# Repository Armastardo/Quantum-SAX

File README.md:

# Quantum-SAX
Digital controller powered by a RP2040

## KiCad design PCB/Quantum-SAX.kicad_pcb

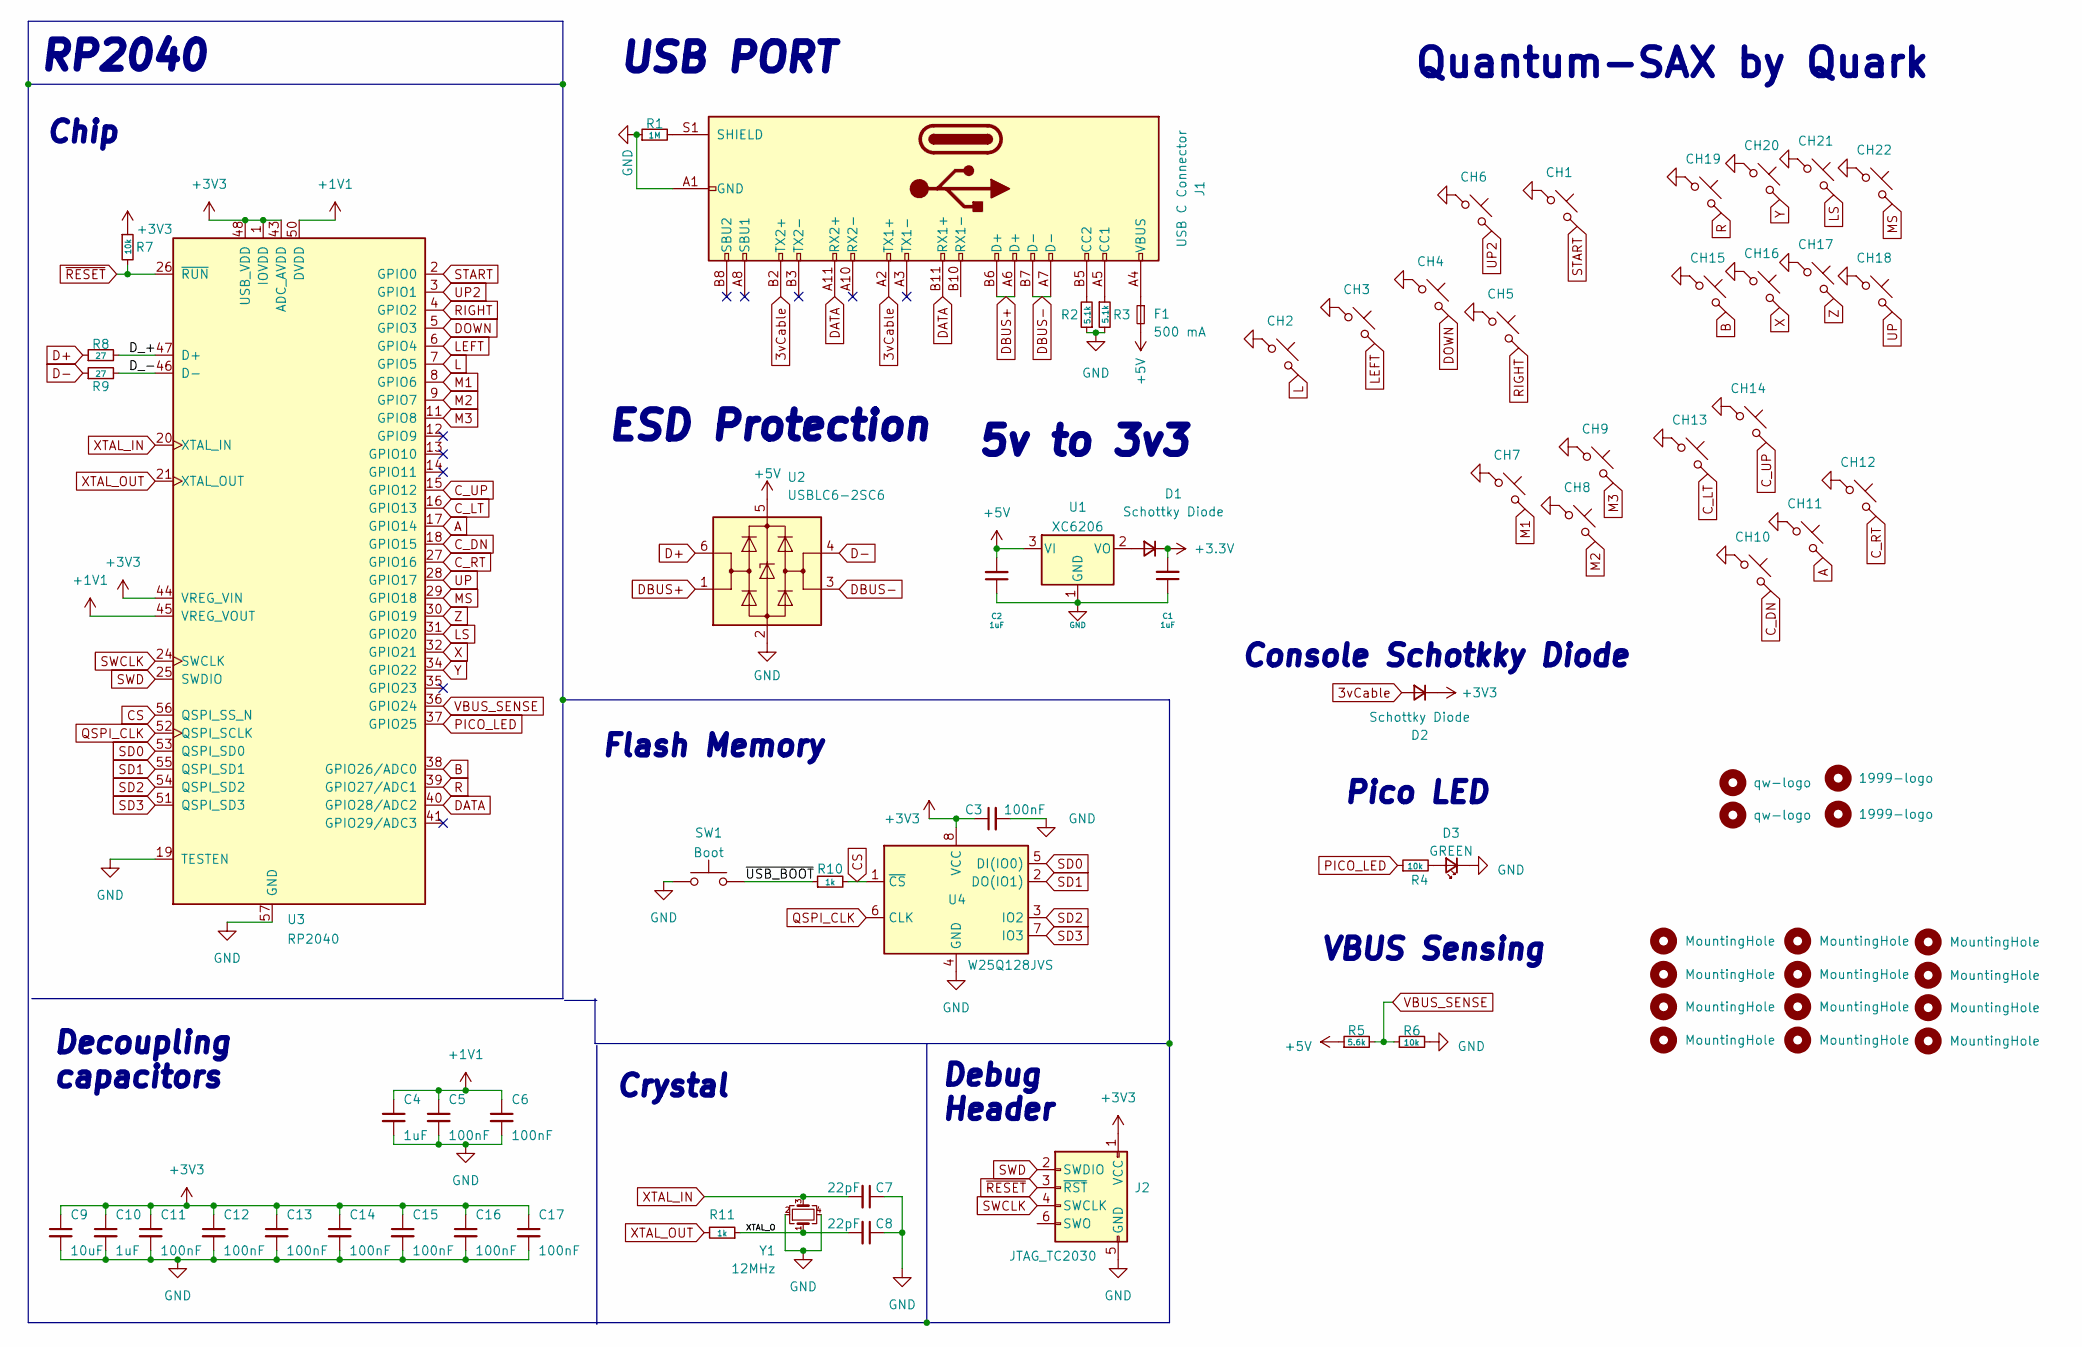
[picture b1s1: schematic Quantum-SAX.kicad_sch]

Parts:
C1, C2, C4, C10: 1uF; C_0402_1005Metric; LCSC C52923
C3, C5, C6, C11, C12, C13, C14, C15, C16, C17: 100nF; C_0402_1005Metric; LCSC C1525
C7, C8: 22pF; C_0402_1005Metric; LCSC C1555
C9: 10uF; C_0402_1005Metric; LCSC C15525
CH1, CH2, CH3, CH4, CH5, CH6, CH7, CH8, CH9, CH10, CH11, CH12, CH13, CH14, CH15, CH16, CH17, CH18, CH19, CH20, CH21, CH22: choc_SW_HS; ModifiedMarbastlibChoc
D1, D2: Schottky Diode; D_SOD-123; LCSC C8598
D3: GREEN; LED_0805_2012Metric
F1: 500 mA; Fuse_1206_3216Metric
H1: qw-logo; qw new logo silk + copper md
H2: qw-logo; qw new logo silk + copper sm
H3, H4: 1999-logo; 1999 logo md
H5, H6, H7, H8, H9, H10, H11, H12, H13, H14, H15, H16: MountingHole; MountingHole_2.2mm_M2
J1: USB C Connector; TYPE-C_24P_QCHT; LCSC C456013
J2: JTAG_TC2030; CON_TC2030_outlined
R1: 1M; R_0603_1608Metric; LCSC C25190
R2, R3: 5.1k; R_0402_1005Metric; LCSC C25744
R4: 10k; R_0402_1005Metric
R5: 5.6k; R_0603_1608Metric
R6: 10k; R_0603_1608Metric
R7: 10k; R_0402_1005Metric; LCSC C25744
R8, R9: 27; R_0603_1608Metric; LCSC C25190
R10, R11: 1k; R_0402_1005Metric; LCSC C11702
SW1: Boot; SW_SPST_SKQG_WithStem; LCSC C5156480
U1: XC6206; SOT-23; LCSC C5446
U2: USBLC6-2SC6; SOT-23-6
U3: RP2040; RP2040-QFN-56; LCSC C2040
U4: W25Q128JVS; SOIC-8_5.23x5.23mm_P1.27mm; LCSC C97521
Y1: 12MHz; Crystal_SMD_3225-4Pin_3.2x2.5mm; LCSC C9002

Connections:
3vCable: D2.2 (A), J1.A2 (TX1+), J1.B2 (TX2+)
+1V1: C4.1, C5.1, C6.1, U3.23 (DVDD), U3.45 (VREG_VOUT), U3.50 (DVDD)
+5V: C2.2, F1.2, R5.1, U1.3 (VI), U2.5 (VBUS)
/D_+: R8.2, U3.47 (D+)
/D_-: R9.2, U3.46 (D-)
/XTAL_O: C8.2, R11.1, Y1.1
/~USB_BOOT: R10.1, SW1.2
A: CH11.2, U3.17 (GPIO14)
B: CH15.2, U3.38 (GPIO26/ADC0)
CS: R10.2, U3.56 (QSPI_SS_N), U4.1 (~CS)
C_DN: CH10.2, U3.18 (GPIO15)
C_LT: CH13.2, U3.16 (GPIO13)
C_RT: CH12.2, U3.27 (GPIO16)
C_UP: CH14.2, U3.15 (GPIO12)
D+: R8.1, U2.6 (I/O1)
D-: R9.1, U2.4 (I/O2)
DATA: J1.A11 (RX2+), J1.B11 (RX1+), U3.40 (GPIO28/ADC2)
DBUS+: J1.A6 (D+), J1.B6 (D+), U2.1 (I/O1)
DBUS-: J1.A7 (D-), J1.B7 (D-), U2.3 (I/O2)
DOWN: CH4.2, U3.5 (GPIO3)
GND: C1.1, C2.1, C3.2, C4.2, C5.2, C6.2, C7.1, C8.1, C9.2, C10.2, C11.2, C12.2, C13.2, C14.2, C15.2, C16.2, C17.2, CH1.1, CH2.1, CH3.1, CH4.1, CH5.1, CH6.1, CH7.1, CH8.1, CH9.1, CH10.1, CH11.1, CH12.1, CH13.1, CH14.1, CH15.1, CH16.1, CH17.1, CH18.1, CH19.1, CH20.1, CH21.1, CH22.1, D3.1 (K), J1.A1 (GND), J1.A12 (GND), J1.B1 (GND), J1.B12 (GND), J2.5 (GND), R1.1, R2.1, R3.2, R6.2, SW1.1, U1.1 (GND), U2.2 (GND), U3.19 (TESTEN), U3.57 (GND), U4.4 (GND), Y1.2, Y1.4
L: CH2.2, U3.7 (GPIO5)
LEFT: CH3.2, U3.6 (GPIO4)
LS: CH21.2, U3.31 (GPIO20)
M1: CH7.2, U3.8 (GPIO6)
M2: CH8.2, U3.9 (GPIO7)
M3: CH9.2, U3.11 (GPIO8)
MS: CH22.2, U3.29 (GPIO18)
unnamed: D1.2 (A), U1.2 (VO)
unnamed: D3.2 (A), R4.2
unnamed: F1.1, J1.A4 (VBUS), J1.A9 (VBUS), J1.B4 (VBUS), J1.B9 (VBUS)
unnamed: J1.A5 (CC1), R3.1
unnamed: J1.B5 (CC2), R2.2
unnamed: J1.S1 (SHIELD), R1.2
PICO_LED: R4.1, U3.37 (GPIO25)
QSPI_CLK: U3.52 (QSPI_SCLK), U4.6 (CLK)
R: CH19.2, U3.39 (GPIO27/ADC1)
RIGHT: CH5.2, U3.4 (GPIO2)
SD0: U3.53 (QSPI_SD0), U4.5 (DI(IO0))
SD1: U3.55 (QSPI_SD1), U4.2 (DO(IO1))
SD2: U3.54 (QSPI_SD2), U4.3 (IO2)
SD3: U3.51 (QSPI_SD3), U4.7 (IO3)
START: CH1.2, U3.2 (GPIO0)
SWCLK: J2.4 (SWCLK), U3.24 (SWCLK)
SWD: J2.2 (SWDIO), U3.25 (SWDIO)
UP: CH18.2, U3.28 (GPIO17)
UP2: CH6.2, U3.3 (GPIO1)
VBUS_SENSE: R5.2, R6.1, U3.36 (GPIO24)
X: CH16.2, U3.32 (GPIO21)
XTAL_IN: C7.2, U3.20 (XTAL_IN), Y1.3
XTAL_OUT: R11.2, U3.21 (XTAL_OUT)
Y: CH20.2, U3.34 (GPIO22)
Z: CH17.2, U3.30 (GPIO19)
~RESET: J2.3 (~RST), R7.2, U3.26 (~RUN)

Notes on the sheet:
USB PORT
Flash Memory
Debug Header
Pico LED
ESD Protection
Console Schotkky Diode
Crystal
VBUS Sensing
Quantum-SAX by Quark
Decoupling capacitors
5v to 3v3
RP2040
Chip

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
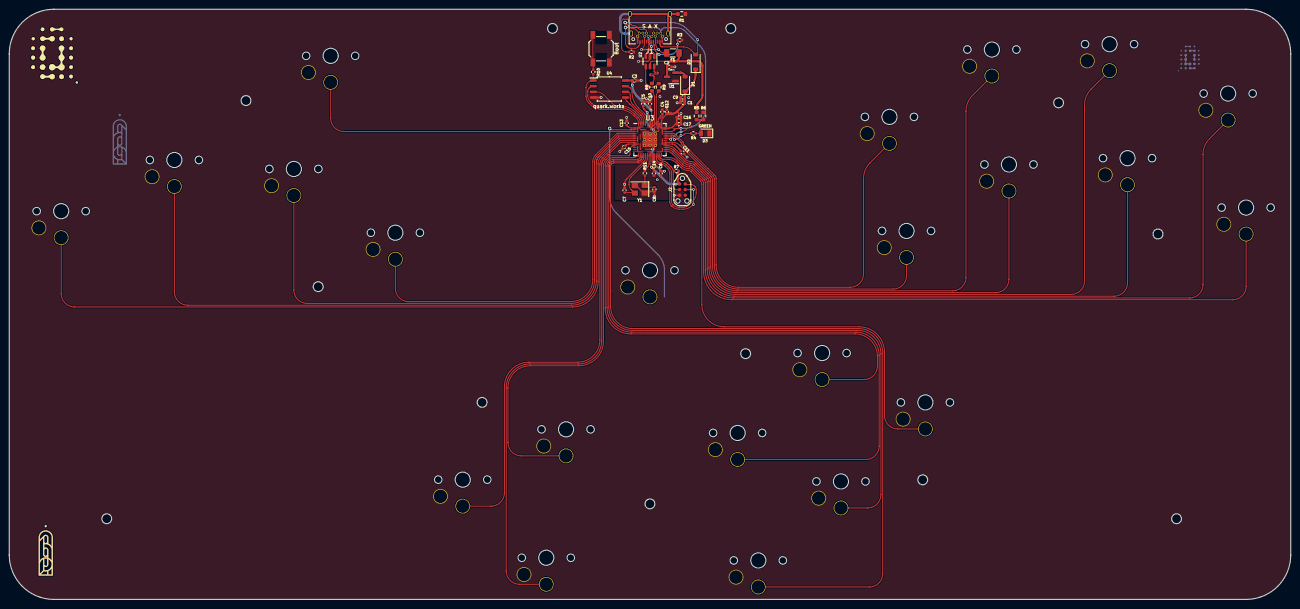
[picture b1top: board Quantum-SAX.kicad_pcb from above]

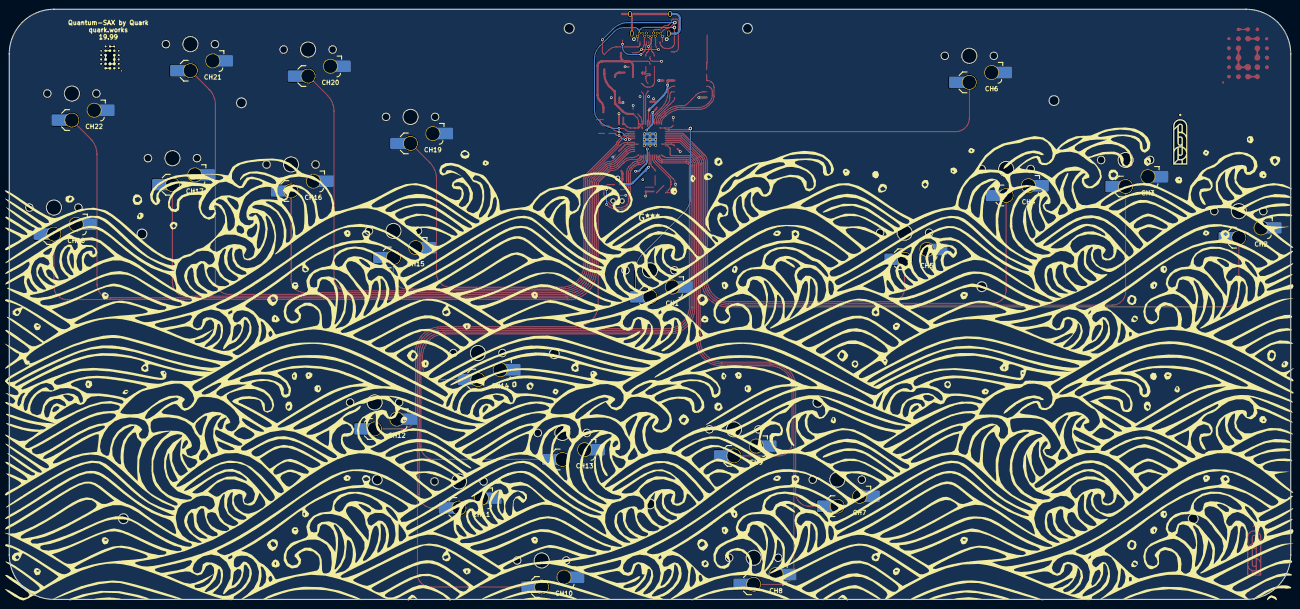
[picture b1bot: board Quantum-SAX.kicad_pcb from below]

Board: 2 copper layers, 287.5 x 132.4 mm, 78 parts (24 on the bottom side), 55 nets.

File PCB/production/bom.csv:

"Designator","Footprint","Quantity","Value","LCSC Part #"
"C1, C10, C2, C4","402","4","1uF","C52923"
"C11, C12, C13, C14, C15, C16, C17, C3, C5, C6","402","10","100nF","C1525"
"C7, C8","402","2","22pF","C1555"
"C9","402","1","10uF","C15525"
"CH1, CH10, CH11, CH12, CH13, CH14, CH15, CH16, CH17, CH18, CH19, CH2, CH20, CH21, CH22, CH3, CH4, CH5, CH6, CH7, CH8, CH9","ModifiedMarbastlibChoc","22","choc_SW_HS",""
"D1, D2","D_SOD-123","2","Schottky Diode","C130880"
"D3","805","1","GREEN",""
"F1","1206","1","500 mA",""
"J1","TYPE-C_24P_QCHT","1","USB C Connector","C456013"
"R1","603","1","1M","C25190"
"R10, R11","402","2","1k","C11702"
"R2, R3","402","2","5.1k","C25744"
"R4, R7","402","2","10k",""
"R5","603","1","5.6k",""
"R6","603","1","10k",""
"R8, R9","603","2","27","C25190"
"SW1","SW_SPST_SKQG_WithStem","1","Boot","C5156480"
"U1","SOT-23","1","XC6206","C5446"
"U2","SOT-23-6","1","USBLC6-2SC6",""
"U3","RP2040-QFN-56","1","RP2040","C2040"
"U4","SOIC-8_5.23x5.23mm_P1.27mm","1","W25Q128JVS","C97521"
"Y1","Crystal_SMD_3225-4Pin_3.2x2.5mm","1","12MHz","C9002"

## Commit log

2023-07-25 Initial component placement
2023-08-04 Finished routing
2023-10-09 Production files and case files
